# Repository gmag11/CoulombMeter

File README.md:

# CoulombMeter
Power meter for low power devices using LTC4150

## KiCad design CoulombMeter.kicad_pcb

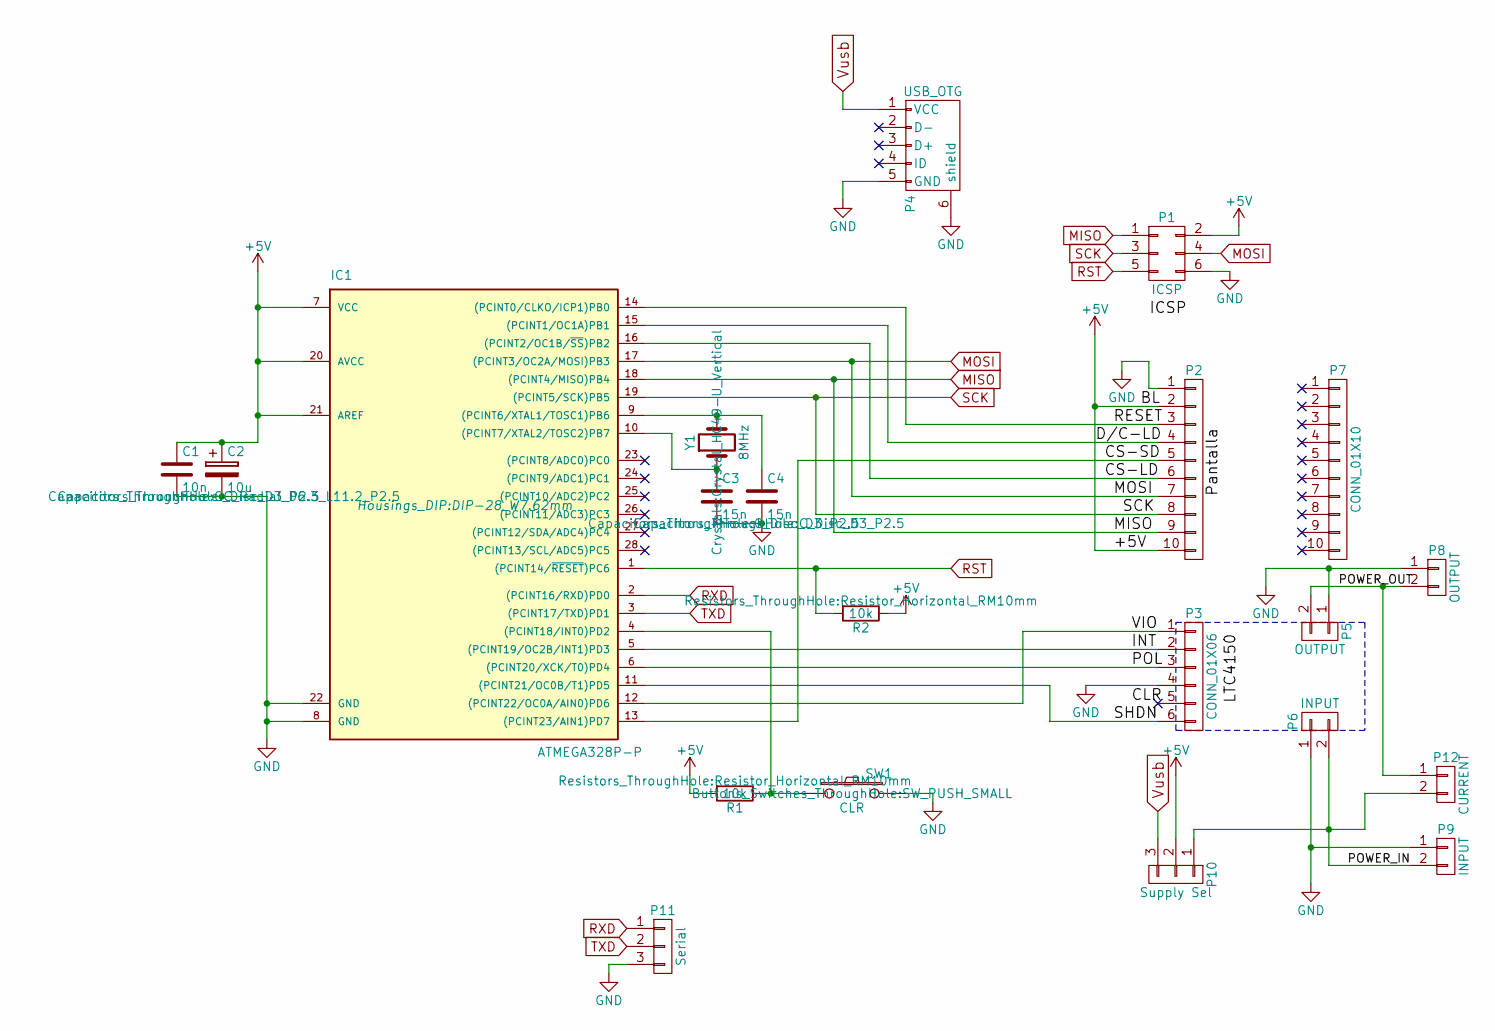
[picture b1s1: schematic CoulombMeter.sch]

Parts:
C1: 10n; C_Disc_D3_P2.5
C2: 10u; C_Radial_D6.3_L11.2_P2.5
C3, C4: 15n; C_Disc_D3_P2.5
IC1: ATMEGA328P-P; DIP-28_W7.62mm
P1: ICSP; Pin_Header_Angled_2x03
P2, P7: CONN_01X10; Socket_Strip_Straight_1x10
P3: CONN_01X06; Socket_Strip_Straight_1x06
P4: USB_OTG; USB_Micro-B
P5: OUTPUT; Socket_Strip_Straight_1x02
P6: INPUT; Socket_Strip_Straight_1x02
P8: OUTPUT; gmkds_3-2-7,62
P9: INPUT; gmkds_3-2-7,62
P10: Supply Sel; Pin_Header_Straight_1x03
P11: Serial; Pin_Header_Straight_1x03
P12: CURRENT; Pin_Header_Angled_1x02_Pitch2.54mm
R1, R2: 10k; Resistor_Horizontal_RM10mm
SW1: CLR; SW_PUSH_SMALL
Y1: 8MHz; Crystal_HC49-U_Vertical

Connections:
+5V: C1.1, C2.1, IC1.7 (VCC), IC1.15 ((PCINT1/OC1A)PB1), IC1.20 (AVCC), IC1.21 (AREF), P1.2, P2.2, P2.4, P2.10, P10.2, R1.2, R2.1
/CS-LD: IC1.16 ((PCINT2/OC1B/~SS~)PB2), P2.6
/CS-SD: IC1.13 ((PCINT23/AIN1)PD7), P2.5
/INT: IC1.5 ((PCINT19/OC2B/INT1)PD3), P3.2
/POL: IC1.6 ((PCINT20/XCK/T0)PD4), P3.3
/POWER_IN: P6.2, P9.2, P10.1, P12.2
/POWER_OUT: P5.2, P8.2, P12.1
/RESET: IC1.14 ((PCINT0/CLKO/ICP1)PB0), P2.3
/SHDN: IC1.11 ((PCINT21/OC0B/T1)PD5), P3.6
/VIO: IC1.12 ((PCINT22/OC0A/AIN0)PD6), P3.1
GND: C1.2, C2.2, C3.2, C4.2, IC1.8 (GND), IC1.22 (GND), P1.6, P2.1, P3.4, P4.5 (GND), P4.6 (shield), P5.1, P6.1, P8.1, P9.1, P11.3, SW1.2
MISO: IC1.18 ((PCINT4/MISO)PB4), P1.1, P2.9
MOSI: IC1.17 ((PCINT3/OC2A/MOSI)PB3), P1.4, P2.7
unnamed: C3.1, IC1.10 ((PCINT7/XTAL2/TOSC2)PB7), Y1.1
unnamed: C4.1, IC1.9 ((PCINT6/XTAL1/TOSC1)PB6), Y1.2
unnamed: IC1.4 ((PCINT18/INT0)PD2), R1.1, SW1.1
RST: IC1.1 ((PCINT14/~RESET~)PC6), P1.5, R2.2
RXD: IC1.2 ((PCINT16/RXD)PD0), P11.1
SCK: IC1.19 ((PCINT5/SCK)PB5), P1.3, P2.8
TXD: IC1.3 ((PCINT17/TXD)PD1), P11.2
Vusb: P4.1 (VCC), P10.3

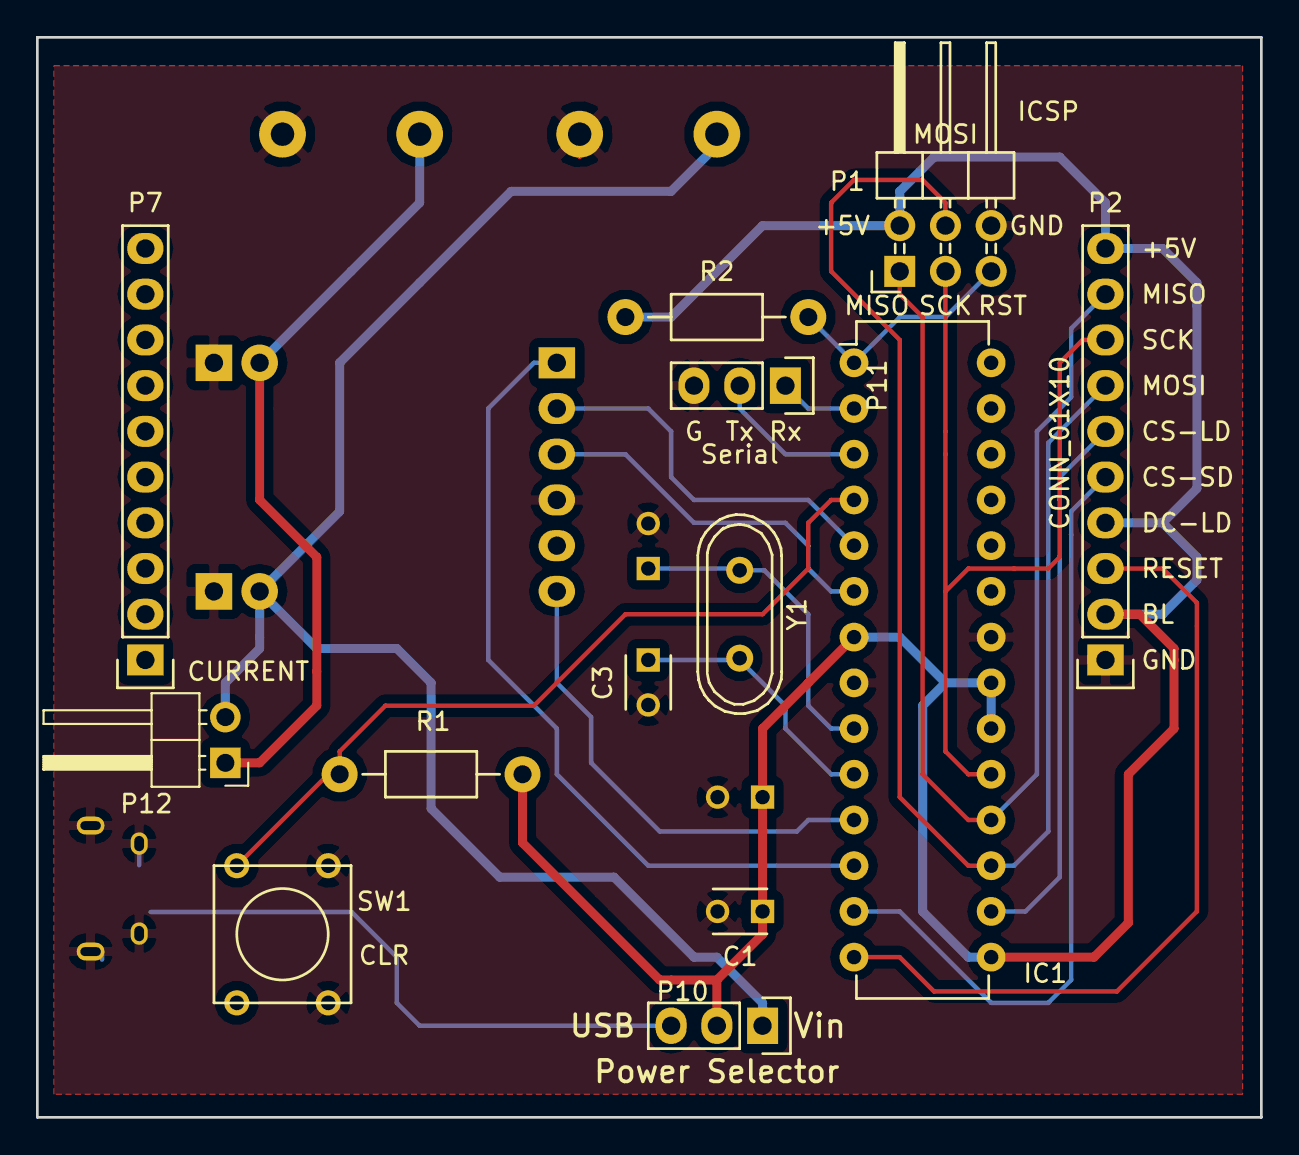
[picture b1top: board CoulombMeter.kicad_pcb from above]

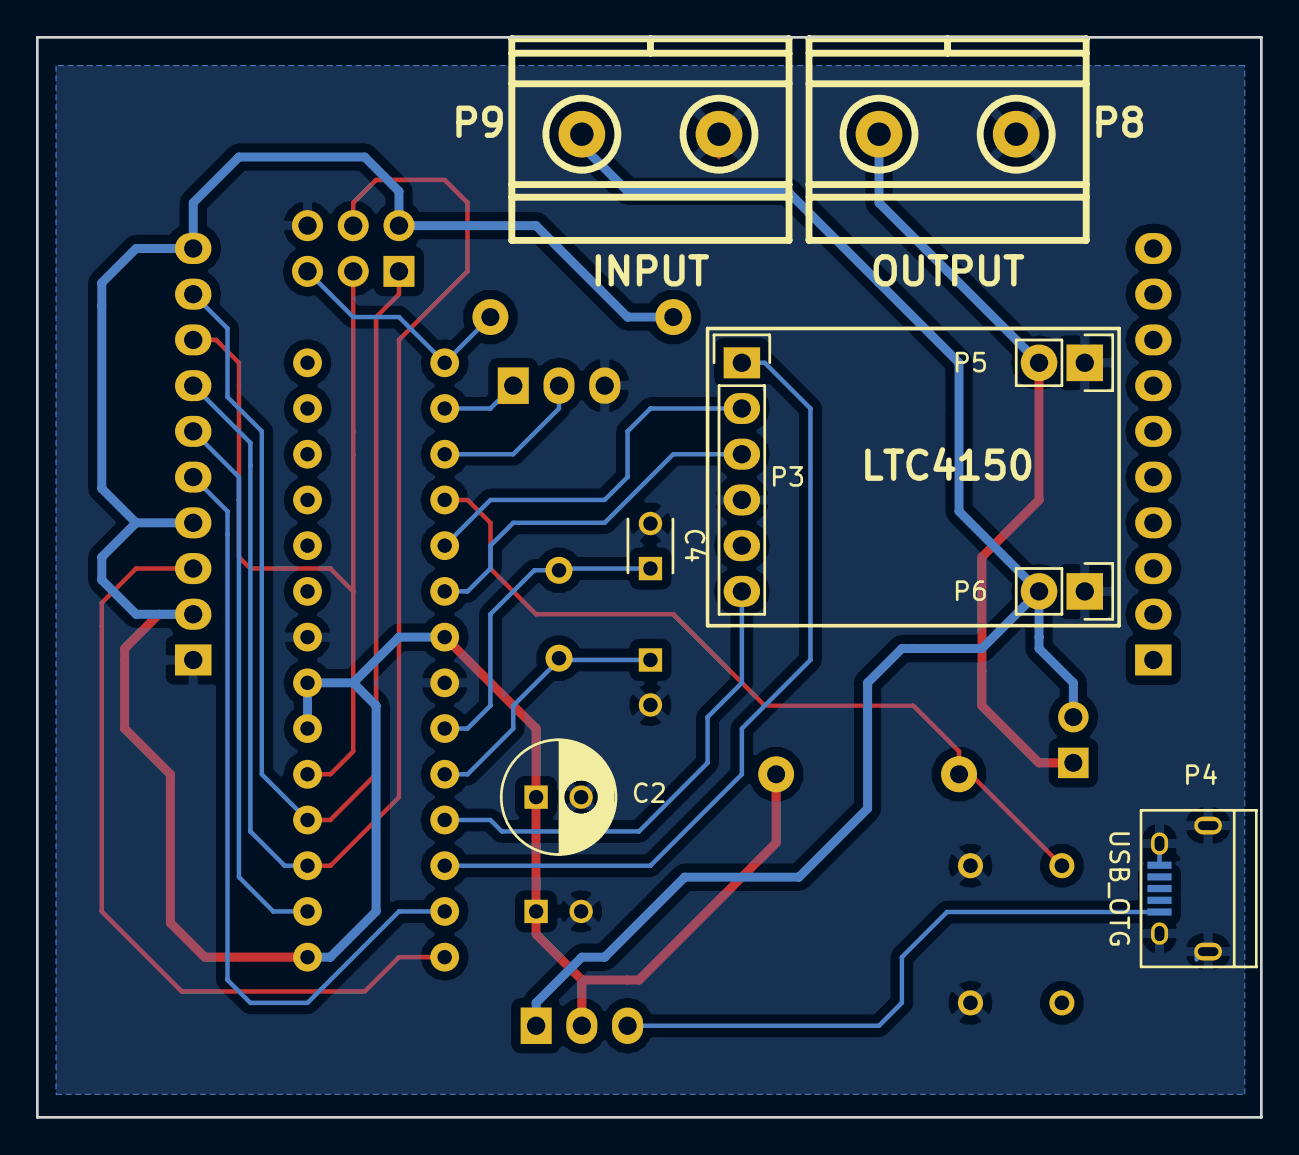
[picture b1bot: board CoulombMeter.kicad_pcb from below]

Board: 2 copper layers, 68.0 x 60.0 mm, 21 parts (8 on the bottom side), 21 nets.

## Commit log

2017-12-19 Final Images
2017-12-19 Fix display socket orientation
2017-12-21 Relocate display
